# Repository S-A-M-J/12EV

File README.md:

# 12EV
 Contains all prototype info and files
 
 CAD -> contains all needed 3d printing files in .step format.

 PCB -> contains all needed info and engineering files for the custom control pcb

 firmware -> contains arduino code for the esp32 on the custom control board

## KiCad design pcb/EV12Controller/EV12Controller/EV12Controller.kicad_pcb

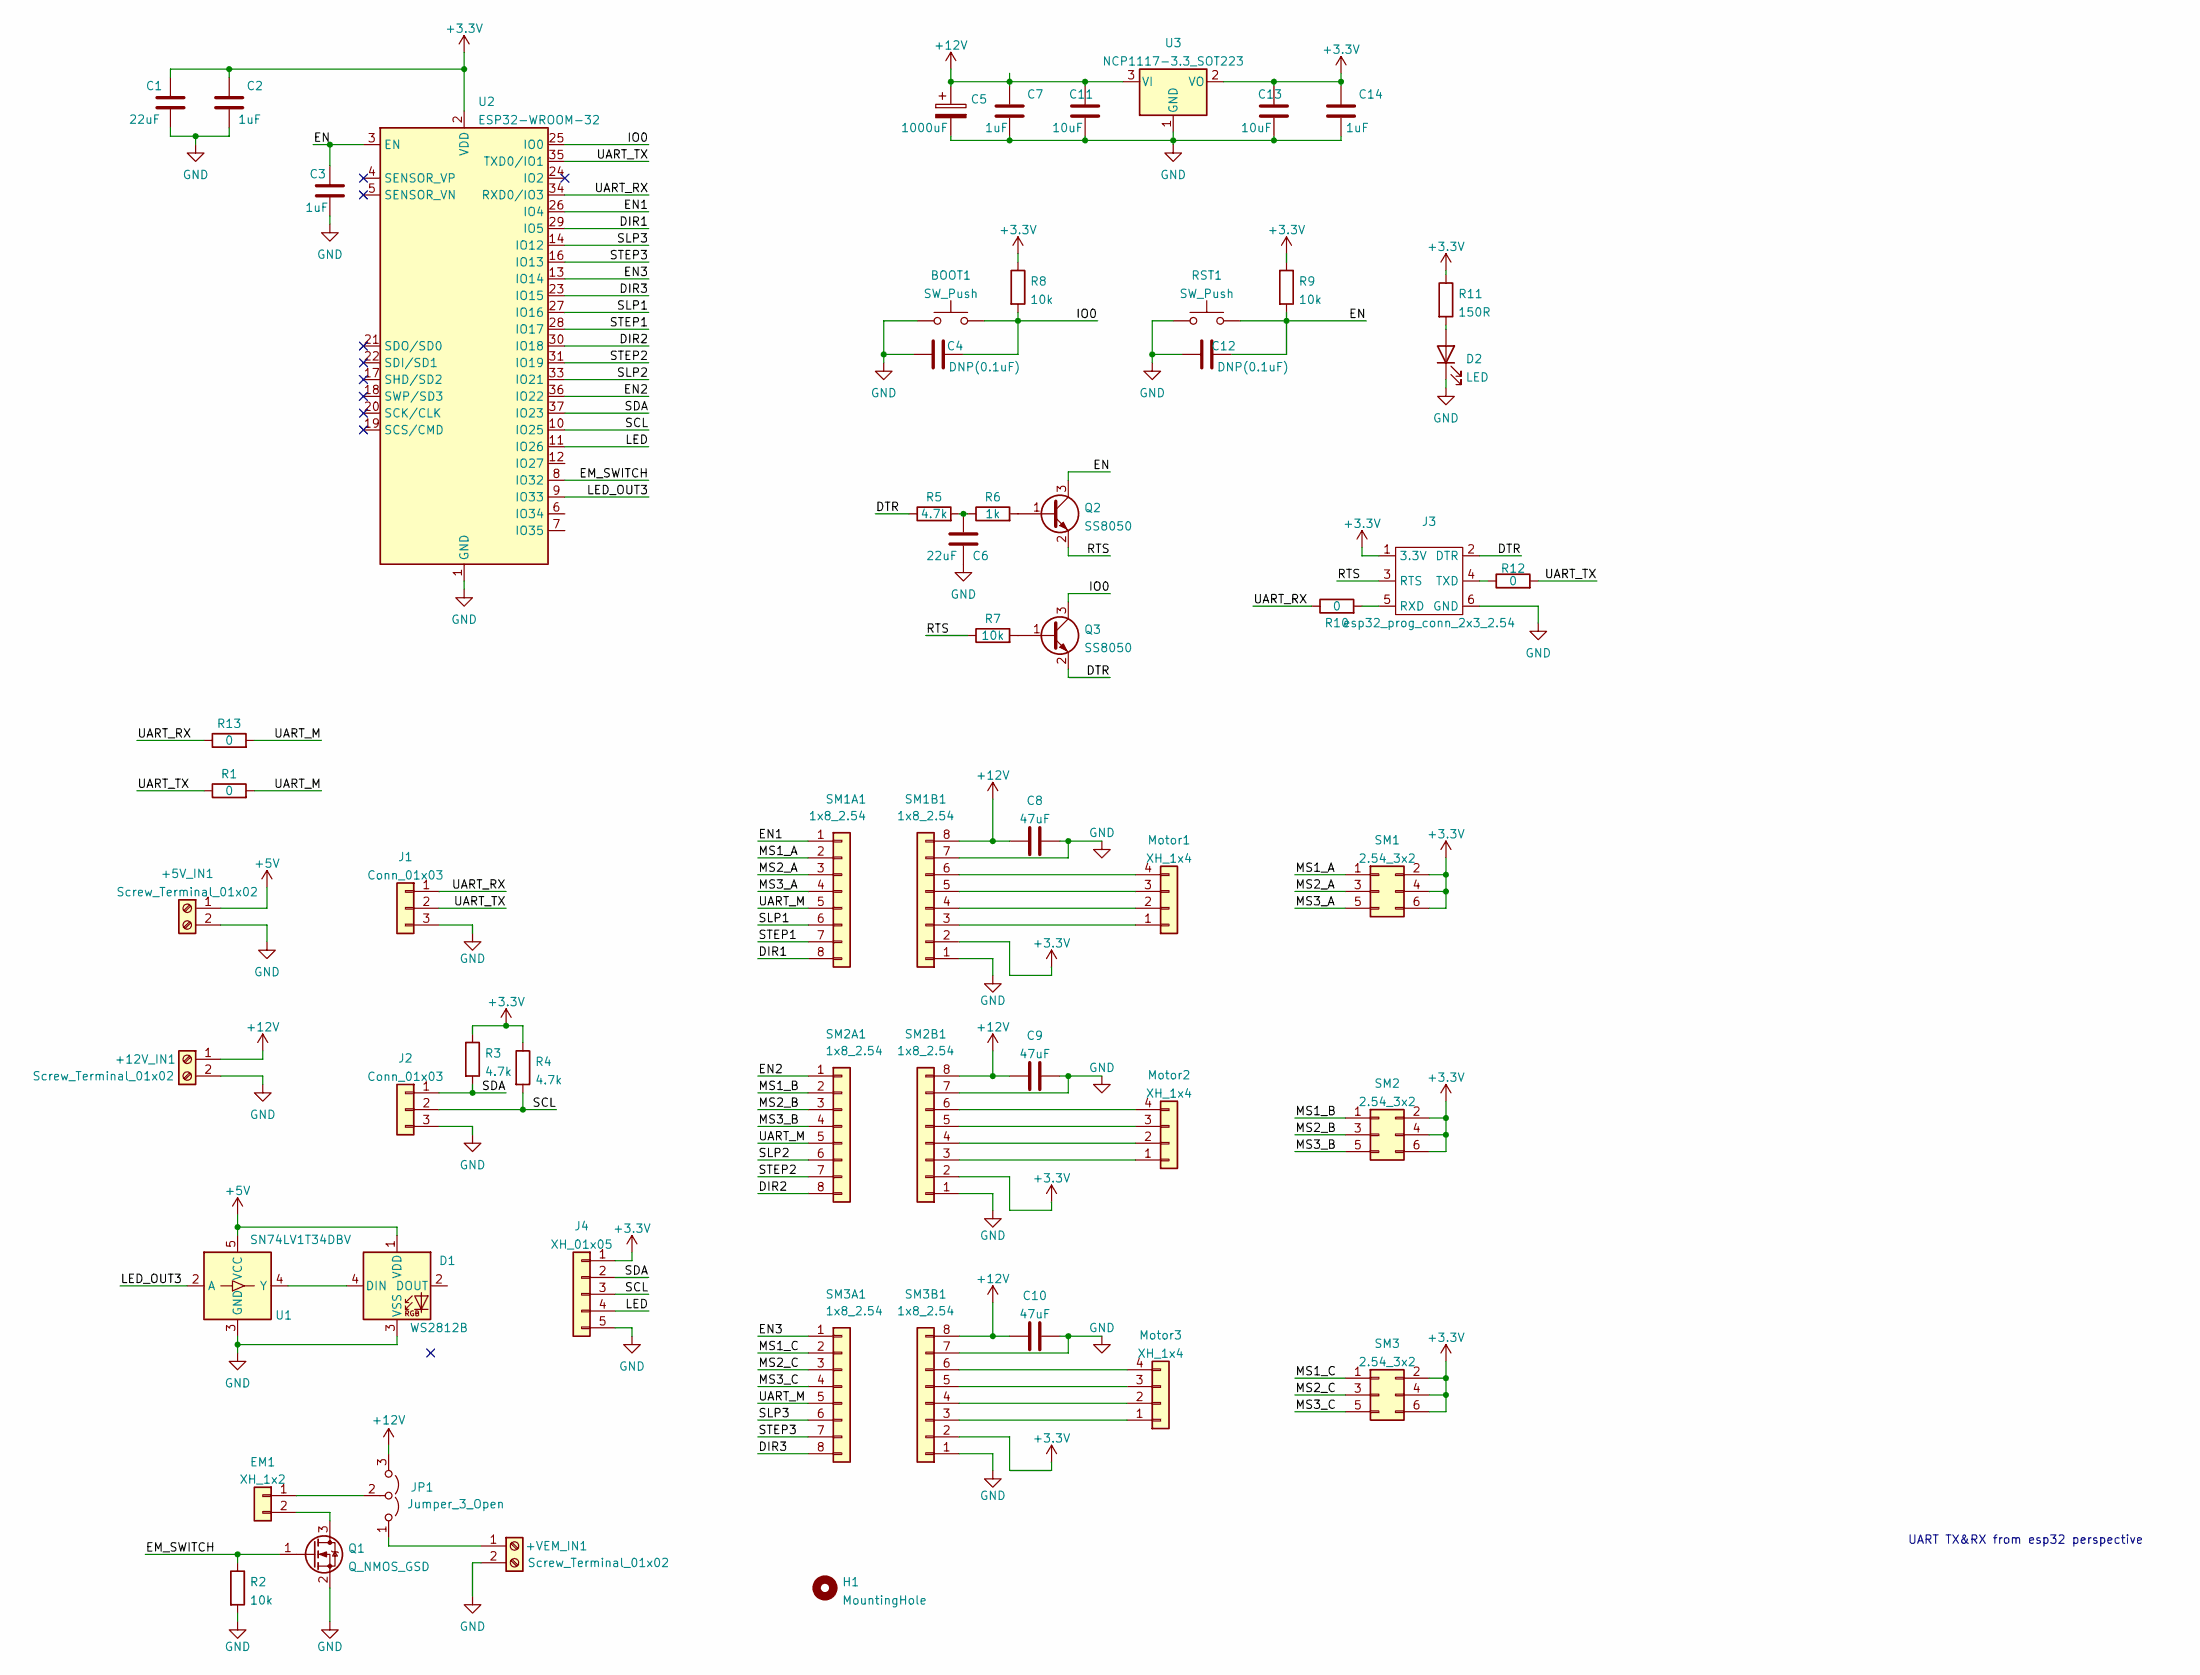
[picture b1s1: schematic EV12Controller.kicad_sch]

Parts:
+5V_IN1, +12V_IN1: Screw_Terminal_01x02; TerminalBlock_bornier-2_P5.08mm
+VEM_IN1: Screw_Terminal_01x02; TerminalBlock_bornier-2_P5.08mm
BOOT1: SW_Push; SW_SPST_CK_RS282G05A3; lcsc C318938
C1, C6: 22uF; C_0603_1608Metric
C2, C3, C7, C14: 1uF; C_0603_1608Metric
C4, C12: DNP(0.1uF); C_0603_1608Metric
C5: 1000uF; CP_Radial_D10.0mm_P5.00mm
C8, C9, C10: 47uF; CP_Elec_6.3x7.7
C11, C13: 10uF; C_0603_1608Metric
D1: WS2812B; LED_WS2812B_PLCC4_5.0x5.0mm_P3.2mm
D2: LED; LED_0805_2012Metric
EM1: XH_1x2; JST_XH_B2B-XH-AM_1x02_P2.50mm_Vertical
H1: MountingHole; MountingHole_3.2mm_M3_DIN965_Pad_TopBottom
J1, J2: Conn_01x03; PinHeader_1x03_P2.54mm_Vertical
J3: esp32_prog_conn_2x3_2.54; PinHeader_2x03_P2.54mm_Vertical
J4: XH_01x05; JST_XH_B5B-XH-AM_1x05_P2.50mm_Vertical
JP1: Jumper_3_Open; SolderJumper-3_P1.3mm_Open_RoundedPad1.0x1.5mm
Motor1, Motor2, Motor3: XH_1x4; JST_XH_B4B-XH-AM_1x04_P2.50mm_Vertical
Q1: Q_NMOS_GSD; SOT-23
Q2, Q3: SS8050; SOT-23
R1, R10, R12, R13: 0; R_0603_1608Metric
R2, R7, R8, R9: 10k; R_0603_1608Metric
R3, R4, R5: 4.7k; R_0603_1608Metric
R6: 1k; R_0603_1608Metric
R11: 150R; R_0603_1608Metric
RST1: SW_Push; SW_SPST_CK_RS282G05A3; lcsc C318938
SM1, SM2, SM3: 2.54_3x2; PinHeader_2x03_P2.54mm_Vertical
SM1A1, SM1B1, SM2A1, SM2B1, SM3A1, SM3B1: 1x8_2.54; PinSocket_1x08_P2.54mm_Vertical
U1: SN74LV1T34DBV; SOT-23-5
U2: ESP32-WROOM-32
U3: NCP1117-3.3_SOT223; SOT-223-3_TabPin2

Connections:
+3V3: C1.1, C2.1, C13.1, C14.1, J3.1 (3.3V), J4.1, R3.1, R4.1, R8.1, R9.1, R11.1, SM1.2, SM1.4, SM1.6, SM1B1.2, SM2.2, SM2.4, SM2.6, SM2B1.2, SM3.2, SM3.4, SM3.6, SM3B1.2, U2.2 (VDD), U3.2 (VO)
+5V: +5V_IN1.1, D1.1 (VDD), U1.5 (VCC)
+12V: +12V_IN1.1, C5.1, C7.1, C8.1, C9.1, C10.1, C11.1, JP1.3 (B), SM1B1.8, SM2B1.8, SM3B1.8, U3.3 (VI)
/DIR1: SM1A1.8, U2.29 (IO5)
/DIR2: SM2A1.8, U2.30 (IO18)
/DIR3: SM3A1.8, U2.23 (IO15)
/DTR: J3.2 (DTR), Q3.2 (E), R5.1
/EM_SWITCH: Q1.1 (G), R2.1, U2.8 (IO32)
/EN: C3.1, C12.2, Q2.3 (C), R9.2, RST1.2, U2.3 (EN)
/EN1: SM1A1.1, U2.26 (IO4)
/EN2: SM2A1.1, U2.36 (IO22)
/EN3: SM3A1.1, U2.13 (IO14)
/IO0: BOOT1.2, C4.2, Q3.3 (C), R8.2, U2.25 (IO0)
/LED: J4.4, U2.11 (IO26)
/LED_OUT3: U1.2 (A), U2.9 (IO33)
/MS1_A: SM1.1, SM1A1.2
/MS1_B: SM2.1, SM2A1.2
/MS1_C: SM3.1, SM3A1.2
/MS2_A: SM1.3, SM1A1.3
/MS2_B: SM2.3, SM2A1.3
/MS2_C: SM3.3, SM3A1.3
/MS3_A: SM1.5, SM1A1.4
/MS3_B: SM2.5, SM2A1.4
/MS3_C: SM3.5, SM3A1.4
/RTS: J3.3 (RTS), Q2.2 (E), R7.1
/SCL: J2.2, J4.3, R4.2, U2.10 (IO25)
/SDA: J2.1, J4.2, R3.2, U2.37 (IO23)
/SLP1: SM1A1.6, U2.27 (IO16)
/SLP2: SM2A1.6, U2.33 (IO21)
/SLP3: SM3A1.6, U2.14 (IO12)
/STEP1: SM1A1.7, U2.28 (IO17)
/STEP2: SM2A1.7, U2.31 (IO19)
/STEP3: SM3A1.7, U2.16 (IO13)
/UART_M: R1.2, R13.2, SM1A1.5, SM2A1.5, SM3A1.5
/UART_RX: J1.1, R10.1, R13.1, U2.34 (RXD0/IO3)
/UART_TX: J1.2, R1.1, R12.2, U2.35 (TXD0/IO1)
GND: +5V_IN1.2, +12V_IN1.2, +VEM_IN1.2, BOOT1.1, C1.2, C2.2, C3.2, C4.1, C5.2, C6.1, C7.2, C8.2, C9.2, C10.2, C11.2, C12.1, C13.2, C14.2, D1.3 (VSS), D2.1 (K), J1.3, J2.3, J3.6 (GND), J4.5, Q1.2 (S), R2.2, RST1.1, SM1B1.1, SM1B1.7, SM2B1.1, SM2B1.7, SM3B1.1, SM3B1.7, U1.3 (GND), U2.1 (GND), U2.15 (GND), U2.38 (GND), U2.39 (GND), U3.1 (GND)
unnamed: +VEM_IN1.1, JP1.1 (A)
unnamed: C6.2, R5.2, R6.1
unnamed: D1.4 (DIN), U1.4 (Y)
unnamed: D2.2 (A), R11.2
unnamed: EM1.1, JP1.2 (C)
unnamed: EM1.2, Q1.3 (D)
unnamed: J3.4 (TXD), R12.1
unnamed: J3.5 (RXD), R10.2
unnamed: Motor1.1, SM1B1.3
unnamed: Motor1.2, SM1B1.4
unnamed: Motor1.3, SM1B1.5
unnamed: Motor1.4, SM1B1.6
unnamed: Motor2.1, SM2B1.3
unnamed: Motor2.2, SM2B1.4
unnamed: Motor2.3, SM2B1.5
unnamed: Motor2.4, SM2B1.6
unnamed: Motor3.1, SM3B1.3
unnamed: Motor3.2, SM3B1.4
unnamed: Motor3.3, SM3B1.5
unnamed: Motor3.4, SM3B1.6
unnamed: Q2.1 (B), R6.2
unnamed: Q3.1 (B), R7.2

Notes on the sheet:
UART TX&RX from esp32 perspective

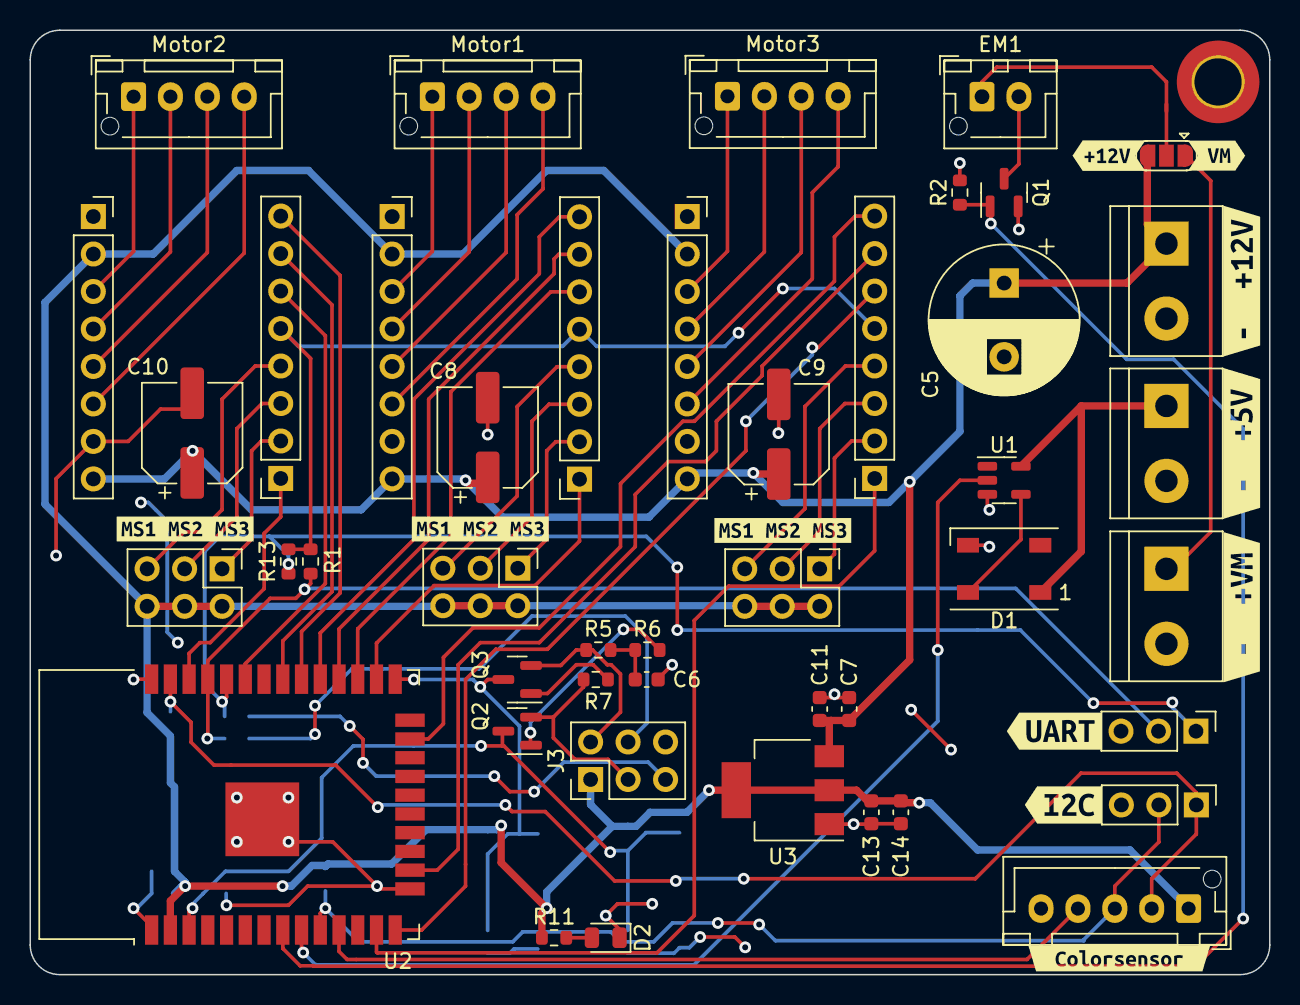
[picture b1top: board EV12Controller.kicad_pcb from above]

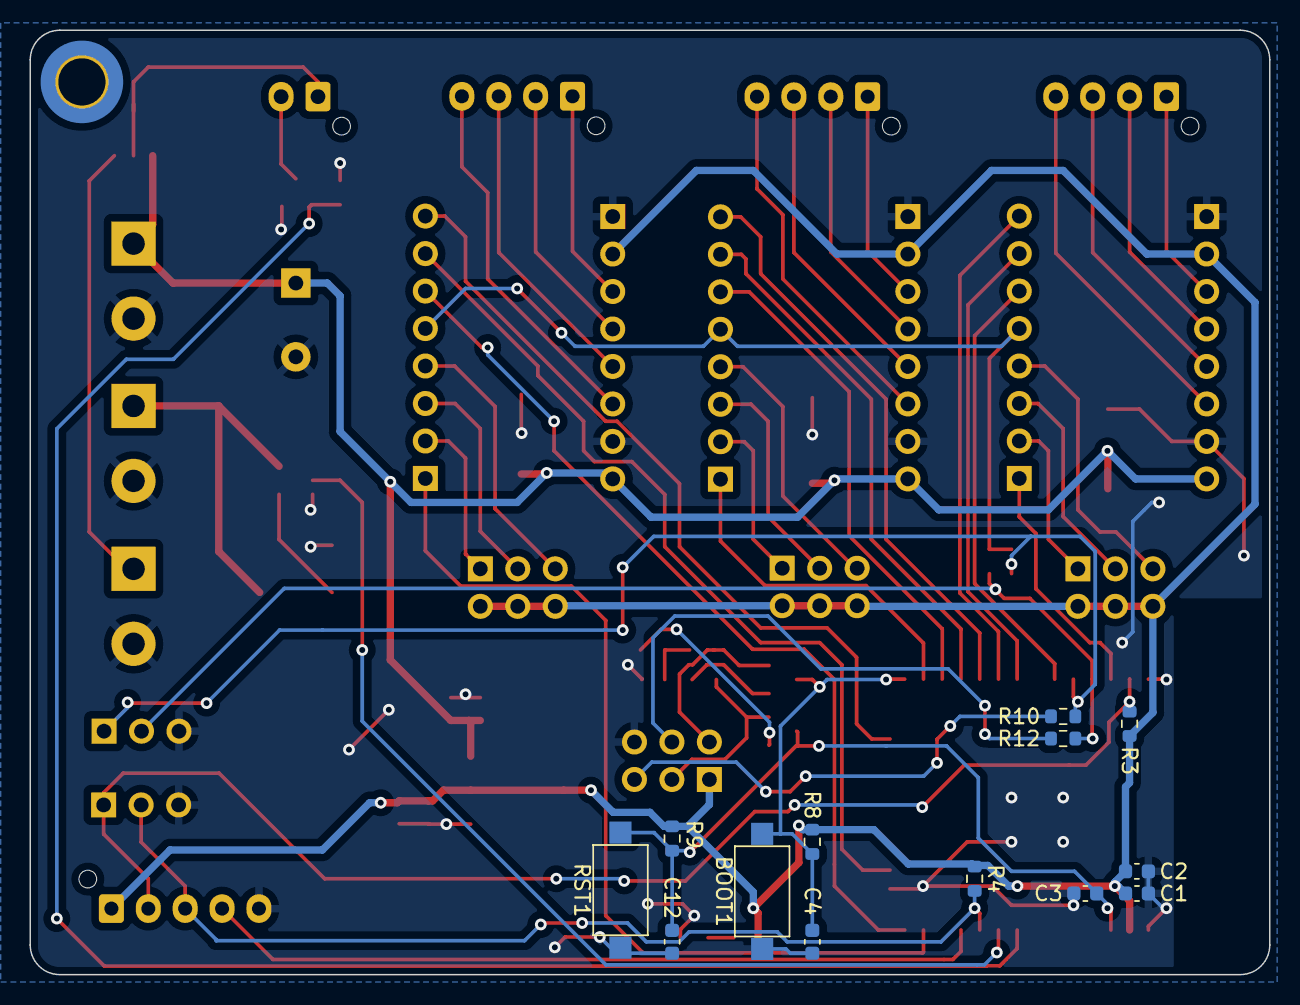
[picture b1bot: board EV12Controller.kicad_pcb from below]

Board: 2 copper layers, 84.0 x 64.0 mm, 70 parts (13 on the bottom side), 59 nets.

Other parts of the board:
kibuzzard-6488F5C4: G***; kibuzzard-6488F5C4
kibuzzard-6488F5F3: G***; kibuzzard-6488F5F3
kibuzzard-6488F56C: G***; kibuzzard-6488F56C
kibuzzard-6488F506: G***; kibuzzard-6488F506
kibuzzard-6488F556: G***; kibuzzard-6488F556
kibuzzard-6488F604: G***; kibuzzard-6488F604
kibuzzard-6488F643, kibuzzard-6488F643#2, kibuzzard-6488F643#3: G***; kibuzzard-6488F643
kibuzzard-6488F768: G***; kibuzzard-6488F768
kibuzzard-6488F773: G***; kibuzzard-6488F773

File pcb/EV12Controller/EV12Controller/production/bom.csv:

Designator,Footprint,Quantity,Value,LCSC Part #
R13,R_0603_1608Metric,1,0,
SM2A1,PinSocket_1x08_P2.54mm_Vertical,1,1x8_2.54,
SM3B1,PinSocket_1x08_P2.54mm_Vertical,1,1x8_2.54,
C10,CP_Elec_6.3x7.7,1,47uF,
SM3,PinHeader_2x03_P2.54mm_Vertical,1,2.54_3x2,
J4,JST_XH_B5B-XH-AM_1x05_P2.50mm_Vertical,1,XH_01x05,
SM1A1,PinSocket_1x08_P2.54mm_Vertical,1,1x8_2.54,
R1,R_0603_1608Metric,1,0,
U2,ESP32-WROOM-32,1,ESP32-WROOM-32,
R2,R_0603_1608Metric,1,10k,
R7,R_0603_1608Metric,1,10k,
C13,C_0603_1608Metric,1,10uF,
SM1,PinHeader_2x03_P2.54mm_Vertical,1,2.54_3x2,
D1,LED_WS2812B_PLCC4_5.0x5.0mm_P3.2mm,1,WS2812B,
JP1,SolderJumper-3_P1.3mm_Open_RoundedPad1.0x1.5mm,1,Jumper_3_Open,
C14,C_0603_1608Metric,1,1uF,
SM2,PinHeader_2x03_P2.54mm_Vertical,1,2.54_3x2,
J2,PinHeader_1x03_P2.54mm_Vertical,1,Conn_01x03,
C7,C_0603_1608Metric,1,1uF,
J1,PinHeader_1x03_P2.54mm_Vertical,1,Conn_01x03,
H1,MountingHole_3.2mm_M3_DIN965_Pad_TopBottom,1,MountingHole,
D2,LED_0805_2012Metric,1,LED,
SM1B1,PinSocket_1x08_P2.54mm_Vertical,1,1x8_2.54,
R11,R_0603_1608Metric,1,150R,
R6,R_0603_1608Metric,1,1k,
U3,SOT-223-3_TabPin2,1,NCP1117-3.3_SOT223,
Motor2,JST_XH_B4B-XH-AM_1x04_P2.50mm_Vertical,1,XH_1x4,
R5,R_0603_1608Metric,1,4.7k,
SM2B1,PinSocket_1x08_P2.54mm_Vertical,1,1x8_2.54,
J3,PinHeader_2x03_P2.54mm_Vertical,1,esp32_prog_conn_2x3_2.54,
Q3,SOT-23,1,SS8050,
C11,C_0603_1608Metric,1,10uF,
+5V_IN1,TerminalBlock_bornier-2_P5.08mm,1,Screw_Terminal_01x02,
SM3A1,PinSocket_1x08_P2.54mm_Vertical,1,1x8_2.54,
Motor3,JST_XH_B4B-XH-AM_1x04_P2.50mm_Vertical,1,XH_1x4,
Motor1,JST_XH_B4B-XH-AM_1x04_P2.50mm_Vertical,1,XH_1x4,
Q2,SOT-23,1,SS8050,
C6,C_0603_1608Metric,1,22uF,
C9,CP_Elec_6.3x7.7,1,47uF,
+12V_IN1,TerminalBlock_bornier-2_P5.08mm,1,Screw_Terminal_01x02,
U1,SOT-23-5,1,SN74LV1T34DBV,
Q1,SOT-23,1,Q_NMOS_GSD,
C8,CP_Elec_6.3x7.7,1,47uF,
+VEM_IN1,TerminalBlock_bornier-2_P5.08mm,1,Screw_Terminal_01x02,
EM1,JST_XH_B2B-XH-AM_1x02_P2.50mm_Vertical,1,XH_1x2,
C5,CP_Radial_D10.0mm_P5.00mm,1,1000uF,
C2,C_0603_1608Metric,1,1uF,
R8,R_0603_1608Metric,1,10k,
C1,C_0603_1608Metric,1,22uF,
R3,R_0603_1608Metric,1,4.7k,
C4,C_0603_1608Metric,1,DNP(0.1uF),
C3,C_0603_1608Metric,1,1uF,
RST1,SW_SPST_CK_RS282G05A3,1,SW_Push,
R10,R_0603_1608Metric,1,0,
R12,R_0603_1608Metric,1,0,
R9,R_0603_1608Metric,1,10k,
BOOT1,SW_SPST_CK_RS282G05A3,1,SW_Push,
R4,R_0603_1608Metric,1,4.7k,
C12,C_0603_1608Metric,1,DNP(0.1uF),

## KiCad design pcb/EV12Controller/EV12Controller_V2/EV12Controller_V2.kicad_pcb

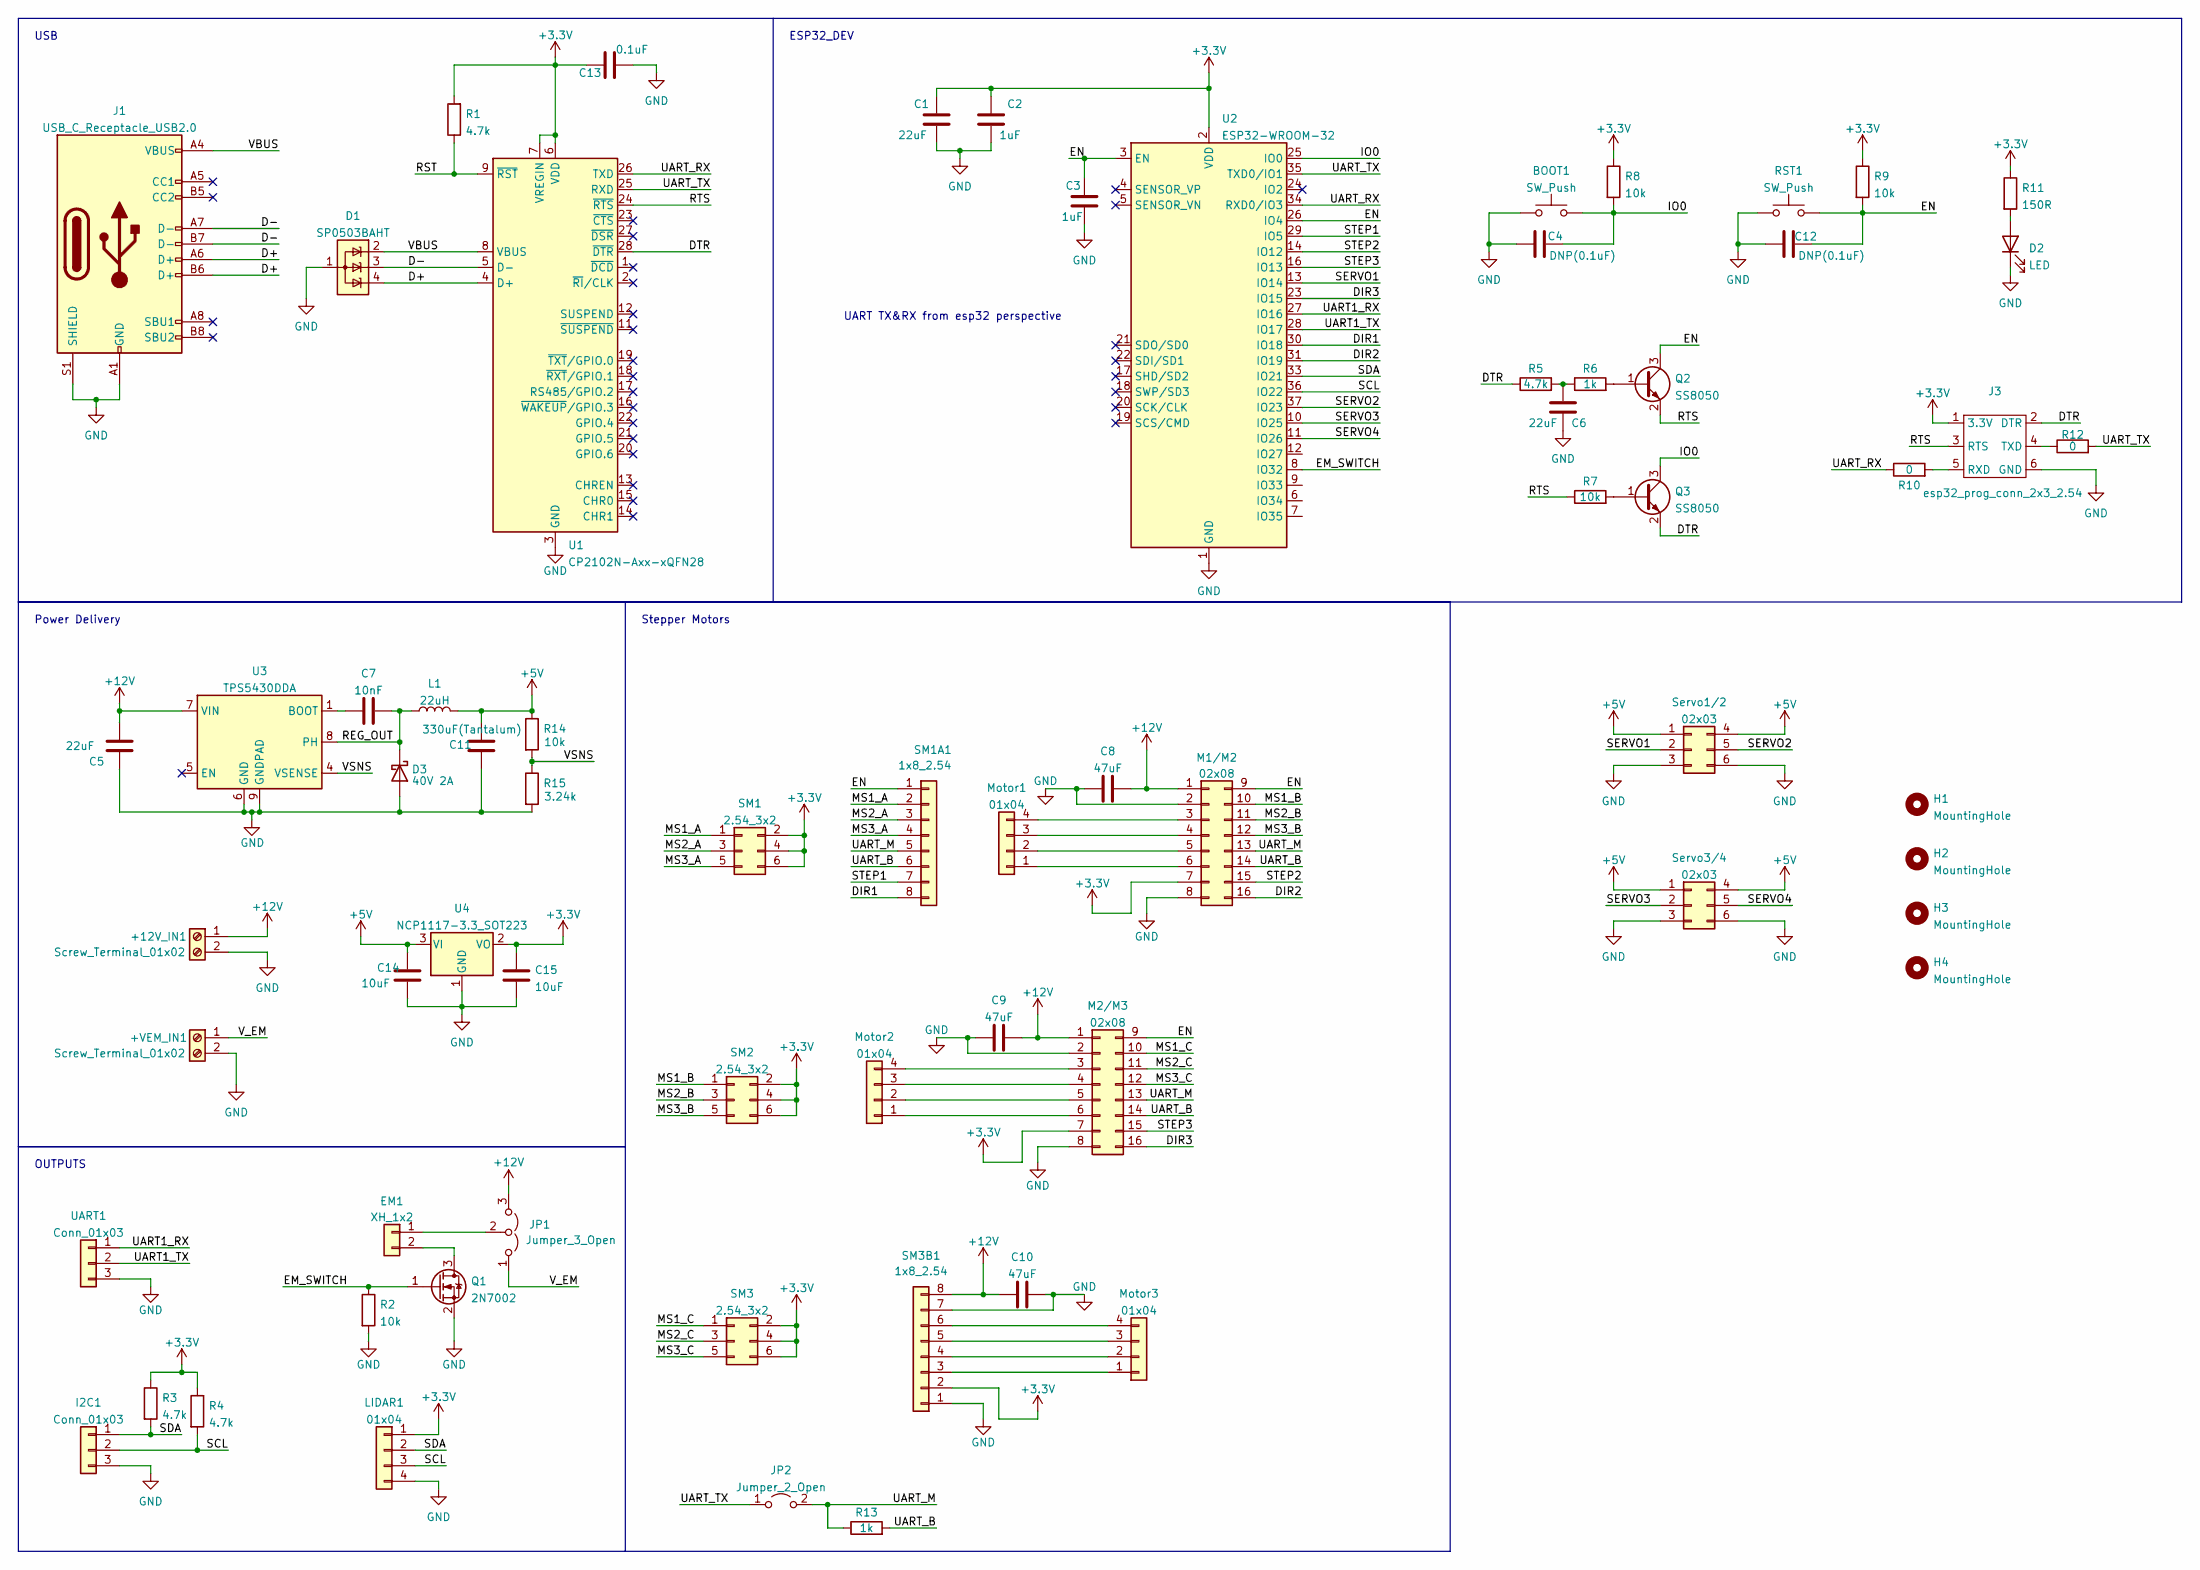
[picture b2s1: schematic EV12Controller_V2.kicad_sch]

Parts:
+12V_IN1: Screw_Terminal_01x02; TerminalBlock_bornier-2_P5.08mm
+VEM_IN1: Screw_Terminal_01x02; TerminalBlock_bornier-2_P5.08mm
BOOT1: SW_Push; SW_SPST_CK_RS282G05A3; lcsc C318938
C1, C6: 22uF; C_0603_1608Metric
C2, C3: 1uF; C_0603_1608Metric
C4, C12: DNP(0.1uF); C_0603_1608Metric
C5: 22uF; C_0805_2012Metric; LCSC C98190
C7: 10nF; C_0603_1608Metric
C8, C9, C10: 47uF; CP_Elec_6.3x7.7
C11: 330uF(Tantalum); C_1206_3216Metric
C13: 0.1uF; C_0805_2012Metric_Pad1.18x1.45mm_HandSolder
C14, C15: 10uF; C_0805_2012Metric_Pad1.18x1.45mm_HandSolder
D1: SP0503BAHT; SOT-143
D2: LED; LED_0805_2012Metric
D3: 40V 2A; D_SMA
EM1: XH_1x2; JST_XH_B2B-XH-AM_1x02_P2.50mm_Vertical
H1, H2, H3, H4: MountingHole; MountingHole_3.2mm_M3_DIN965_Pad_TopBottom
I2C1: Conn_01x03; PinHeader_1x03_P2.54mm_Vertical
J1: USB_C_Receptacle_USB2.0; USB_C_Receptacle_HRO_TYPE-C-31-M-12
J3: esp32_prog_conn_2x3_2.54; PinHeader_2x03_P2.54mm_Vertical
JP1: Jumper_3_Open; SolderJumper-3_P1.3mm_Open_RoundedPad1.0x1.5mm
JP2: Jumper_2_Open; SolderJumper-2_P1.3mm_Open_RoundedPad1.0x1.5mm
L1: 22uH; L_Bourns_SRP7028A_7.3x6.6mm
LIDAR1: 01x04; PinHeader_1x04_P2.54mm_Vertical_SMD_Pin1Left
M1/M2, M2/M3: 02x08; PinSocket_2x08_P2.54mm_Vertical_SMD
Motor1, Motor2, Motor3: 01x04; PinHeader_1x04_P2.54mm_Vertical_SMD_Pin1Left
Q1: 2N7002; SOT-23
Q2, Q3: SS8050; SOT-23
R1: 4.7k; R_0805_2012Metric
R2, R7, R8, R9, R14: 10k; R_0603_1608Metric
R3, R4, R5: 4.7k; R_0603_1608Metric
R6, R13: 1k; R_0603_1608Metric
R10, R12: 0; R_0603_1608Metric
R11: 150R; R_0603_1608Metric
R15: 3.24k; R_0805_2012Metric
RST1: SW_Push; SW_SPST_CK_RS282G05A3; lcsc C318938
SM1, SM2, SM3: 2.54_3x2; PinHeader_2x03_P2.54mm_Vertical
SM1A1, SM3B1: 1x8_2.54; PinSocket_1x08_P2.54mm_Vertical_SMD_Pin1Left
Servo1/2, Servo3/4: 02x03; PinHeader_2x03_P2.54mm_Vertical_SMD
U1: CP2102N-Axx-xQFN28; QFN-28-1EP_5x5mm_P0.5mm_EP3.35x3.35mm
U2: ESP32-WROOM-32
U3: TPS5430DDA; TI_SO-PowerPAD-8_ThermalVias
U4: NCP1117-3.3_SOT223; SOT-223-3_TabPin2
UART1: Conn_01x03; PinHeader_1x03_P2.54mm_Vertical

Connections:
+3V3: C1.1, C2.1, C13.1, C15.1, J3.1 (3.3V), LIDAR1.1, M1/M2.7, M2/M3.7, R1.2, R3.1, R4.1, R8.1, R9.1, R11.1, SM1.2, SM1.4, SM1.6, SM2.2, SM2.4, SM2.6, SM3.2, SM3.4, SM3.6, SM3B1.2, U1.6 (VDD), U1.7 (VREGIN), U2.2 (VDD), U4.2 (VO)
+5V: C11.1, C14.1, L1.2, R14.1, Servo1/2.1, Servo1/2.4, Servo3/4.1, Servo3/4.4, U4.3 (VI)
+12V: +12V_IN1.1, C5.1, C8.1, C9.1, C10.1, JP1.3 (B), M1/M2.1, M2/M3.1, SM3B1.8, U3.7 (VIN)
/D+: D1.4 (K), J1.A6 (D+), J1.B6 (D+), U1.4 (D+)
/D-: D1.3 (K), J1.A7 (D-), J1.B7 (D-), U1.5 (D-)
/DIR1: SM1A1.8, U2.30 (IO18)
/DIR2: M1/M2.16, U2.31 (IO19)
/DIR3: M2/M3.16, U2.23 (IO15)
/DTR: J3.2 (DTR), Q3.2 (E), R5.1, U1.28 (~DTR)
/EM_SWITCH: Q1.1 (G), R2.1, U2.8 (IO32)
/EN: C3.1, C12.2, M1/M2.9, M2/M3.9, Q2.3 (C), R9.2, RST1.2, SM1A1.1, U2.3 (EN), U2.26 (IO4)
/IO0: BOOT1.2, C4.2, Q3.3 (C), R8.2, U2.25 (IO0)
/MS1_A: SM1.1, SM1A1.2
/MS1_B: M1/M2.10, SM2.1
/MS1_C: M2/M3.10, SM3.1
/MS2_A: SM1.3, SM1A1.3
/MS2_B: M1/M2.11, SM2.3
/MS2_C: M2/M3.11, SM3.3
/MS3_A: SM1.5, SM1A1.4
/MS3_B: M1/M2.12, SM2.5
/MS3_C: M2/M3.12, SM3.5
/REG_OUT: C7.2, D3.1 (K), L1.1, U3.8 (PH)
/RST: R1.1, U1.9 (~RST)
/RTS: J3.3 (RTS), Q2.2 (E), R7.1, U1.24 (~RTS)
/SCL: I2C1.2, LIDAR1.3, R4.2, U2.36 (IO22)
/SDA: I2C1.1, LIDAR1.2, R3.2, U2.33 (IO21)
/SERVO1: Servo1/2.2, U2.13 (IO14)
/SERVO2: Servo1/2.5, U2.37 (IO23)
/SERVO3: Servo3/4.2, U2.10 (IO25)
/SERVO4: Servo3/4.5, U2.11 (IO26)
/STEP1: SM1A1.7, U2.29 (IO5)
/STEP2: M1/M2.15, U2.14 (IO12)
/STEP3: M2/M3.15, U2.16 (IO13)
/UART1_RX: U2.27 (IO16), UART1.1
/UART1_TX: U2.28 (IO17), UART1.2
/UART_B: M1/M2.14, M2/M3.14, R13.2, SM1A1.6
/UART_M: JP2.2 (B), M1/M2.13, M2/M3.13, R13.1, SM1A1.5
/UART_RX: R10.1, U1.26 (TXD), U2.34 (RXD0/IO3)
/UART_TX: JP2.1 (A), R12.2, U1.25 (RXD), U2.35 (TXD0/IO1)
/VBUS: D1.2 (K), J1.A4 (VBUS), J1.A9 (VBUS), J1.B4 (VBUS), J1.B9 (VBUS), U1.8 (VBUS)
/VSNS: R14.2, R15.1, U3.4 (VSENSE)
/V_EM: +VEM_IN1.1, JP1.1 (A)
GND: +12V_IN1.2, +VEM_IN1.2, BOOT1.1, C1.2, C2.2, C3.2, C4.1, C5.2, C6.1, C8.2, C9.2, C10.2, C11.2, C12.1, C13.2, C14.2, C15.2, D1.1 (A), D2.1 (K), D3.2 (A), I2C1.3, J1.A1 (GND), J1.A12 (GND), J1.B1 (GND), J1.B12 (GND), J1.S1 (SHIELD), J3.6 (GND), LIDAR1.4, M1/M2.2, M1/M2.8, M2/M3.2, M2/M3.8, Q1.2 (S), R2.2, R15.2, RST1.1, SM3B1.1, SM3B1.7, Servo1/2.3, Servo1/2.6, Servo3/4.3, Servo3/4.6, U1.3 (GND), U1.29 (GND), U2.1 (GND), U2.15 (GND), U2.38 (GND), U2.39 (GND), U3.6 (GND), U3.9 (GNDPAD), U4.1 (GND), UART1.3
unnamed: C6.2, R5.2, R6.1
unnamed: C7.1, U3.1 (BOOT)
unnamed: D2.2 (A), R11.2
unnamed: EM1.1, JP1.2 (C)
unnamed: EM1.2, Q1.3 (D)
unnamed: J3.4 (TXD), R12.1
unnamed: J3.5 (RXD), R10.2
unnamed: M1/M2.3, Motor1.4
unnamed: M1/M2.4, Motor1.3
unnamed: M1/M2.5, Motor1.2
unnamed: M1/M2.6, Motor1.1
unnamed: M2/M3.3, Motor2.4
unnamed: M2/M3.4, Motor2.3
unnamed: M2/M3.5, Motor2.2
unnamed: M2/M3.6, Motor2.1
unnamed: Motor3.1, SM3B1.3
unnamed: Motor3.2, SM3B1.4
unnamed: Motor3.3, SM3B1.5
unnamed: Motor3.4, SM3B1.6
unnamed: Q2.1 (B), R6.2
unnamed: Q3.1 (B), R7.2

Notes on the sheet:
UART TX&RX from esp32 perspective
OUTPUTS
USB
Power Delivery
ESP32_DEV
Stepper Motors

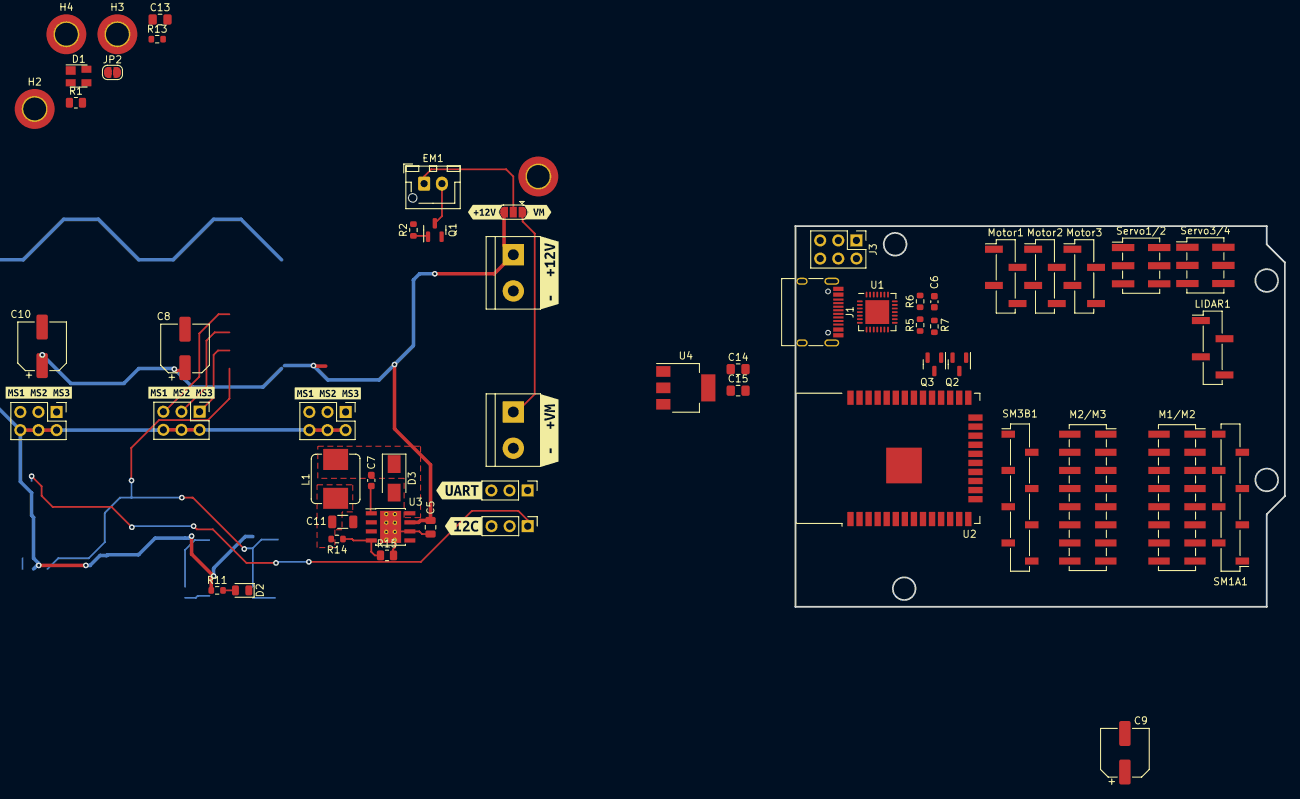
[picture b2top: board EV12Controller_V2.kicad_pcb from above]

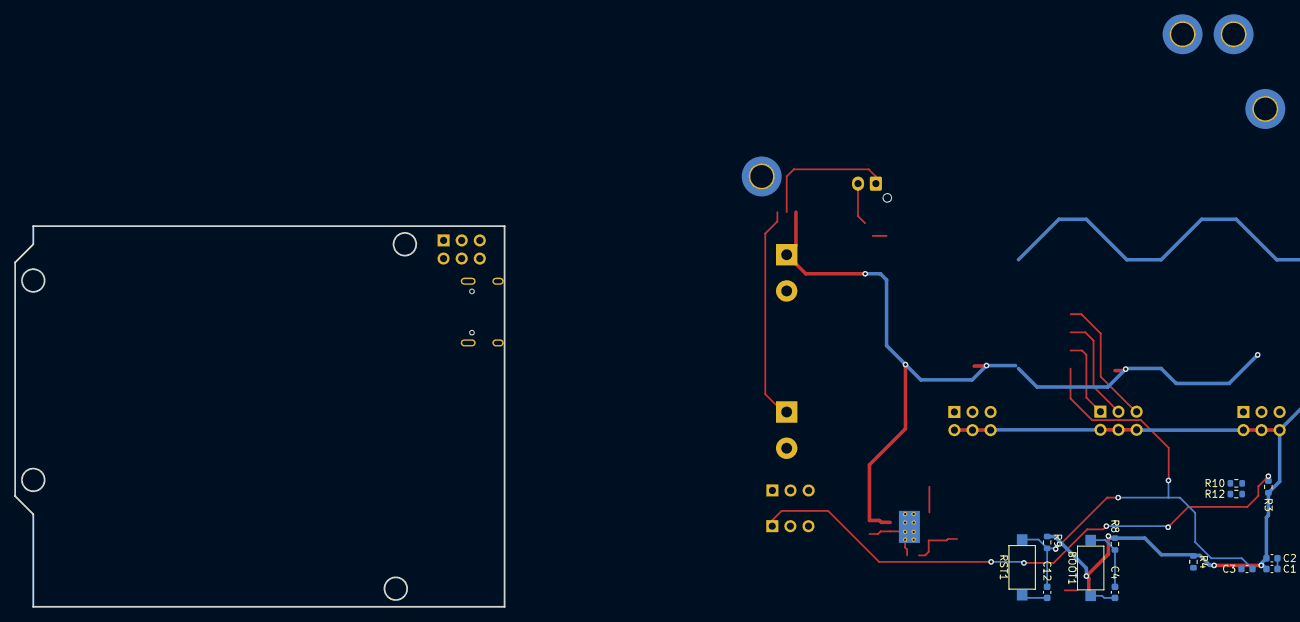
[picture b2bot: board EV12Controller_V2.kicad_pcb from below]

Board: 2 copper layers, 68.6 x 53.3 mm, 78 parts (13 on the bottom side), 64 nets.

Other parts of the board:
kibuzzard-6488F5F3: G***; kibuzzard-6488F5F3
kibuzzard-6488F56C: G***; kibuzzard-6488F56C
kibuzzard-6488F506: G***; kibuzzard-6488F506
kibuzzard-6488F604: G***; kibuzzard-6488F604
kibuzzard-6488F643, kibuzzard-6488F643#2, kibuzzard-6488F643#3: G***; kibuzzard-6488F643
kibuzzard-6488F768: G***; kibuzzard-6488F768
kibuzzard-6488F773: G***; kibuzzard-6488F773

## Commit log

2023-07-10 added all files
2023-07-11 updated firmware
2023-07-11 updated pcb
2023-07-11 updated file structure
